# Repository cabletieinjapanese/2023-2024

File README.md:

repository for robocup bot, 2024 Singapore Robocup Open season

*updated 5 apr 2024*
## team, roles
loh hao yuan - elec, programming

lee yu zhe - mech, programming

cruz low, oliver ong - logistics, soldering

## final results
(5 apr 2024) 
due to a variety of factors (including misinterpretation of registration information, delays in robot production, lack of time for organiser to make adjustments), we were unable to participate in the 2024 Singapore Robocup Open.

throughout the past year, we've learnt a lot about the workings of a robocup bot, and we'll be back next year to finally prove our worth

we're currently working to finish up and polish our bot, such that we can run a few scrim games before starting anew with our bot for the 2024-2025 season.

## remarks
* everything here is half cooked spaghetti
    * we spent a lot of our time this year trying to figure things out, so a lot of stuff here is the result of trial and error
    * i guess our learning can be shown through the different versions, but theres many many areas which have a lot of potential for improvement
* version control
    * we didn't really use our github repository that much, which is a really bad practice
    * furthermore, one of our members has still not figured out how version control works, and consistently asks me to "help (him) push the code"  

## thanks
* [Sentinels Robotics](https://github.com/senrobo)
    * [@vincentcayadi](https://github.com/vincentcayadi) for his advice regarding the sport and life as a whole, his boundless enthusiasm, faith in our capabilities and good humour
    * [@shuanluck](https://github.com/shuanluck), [@DavidLow22](https://github.com/DavidLow22), and Tan Kian Wu for advice in all areas of robocup
* [Ducc Robotics](https://github.com/8076ducc)
    * [@neohaojun](https://github.com/neohaojun) for guidance and advice with regards to budgeting

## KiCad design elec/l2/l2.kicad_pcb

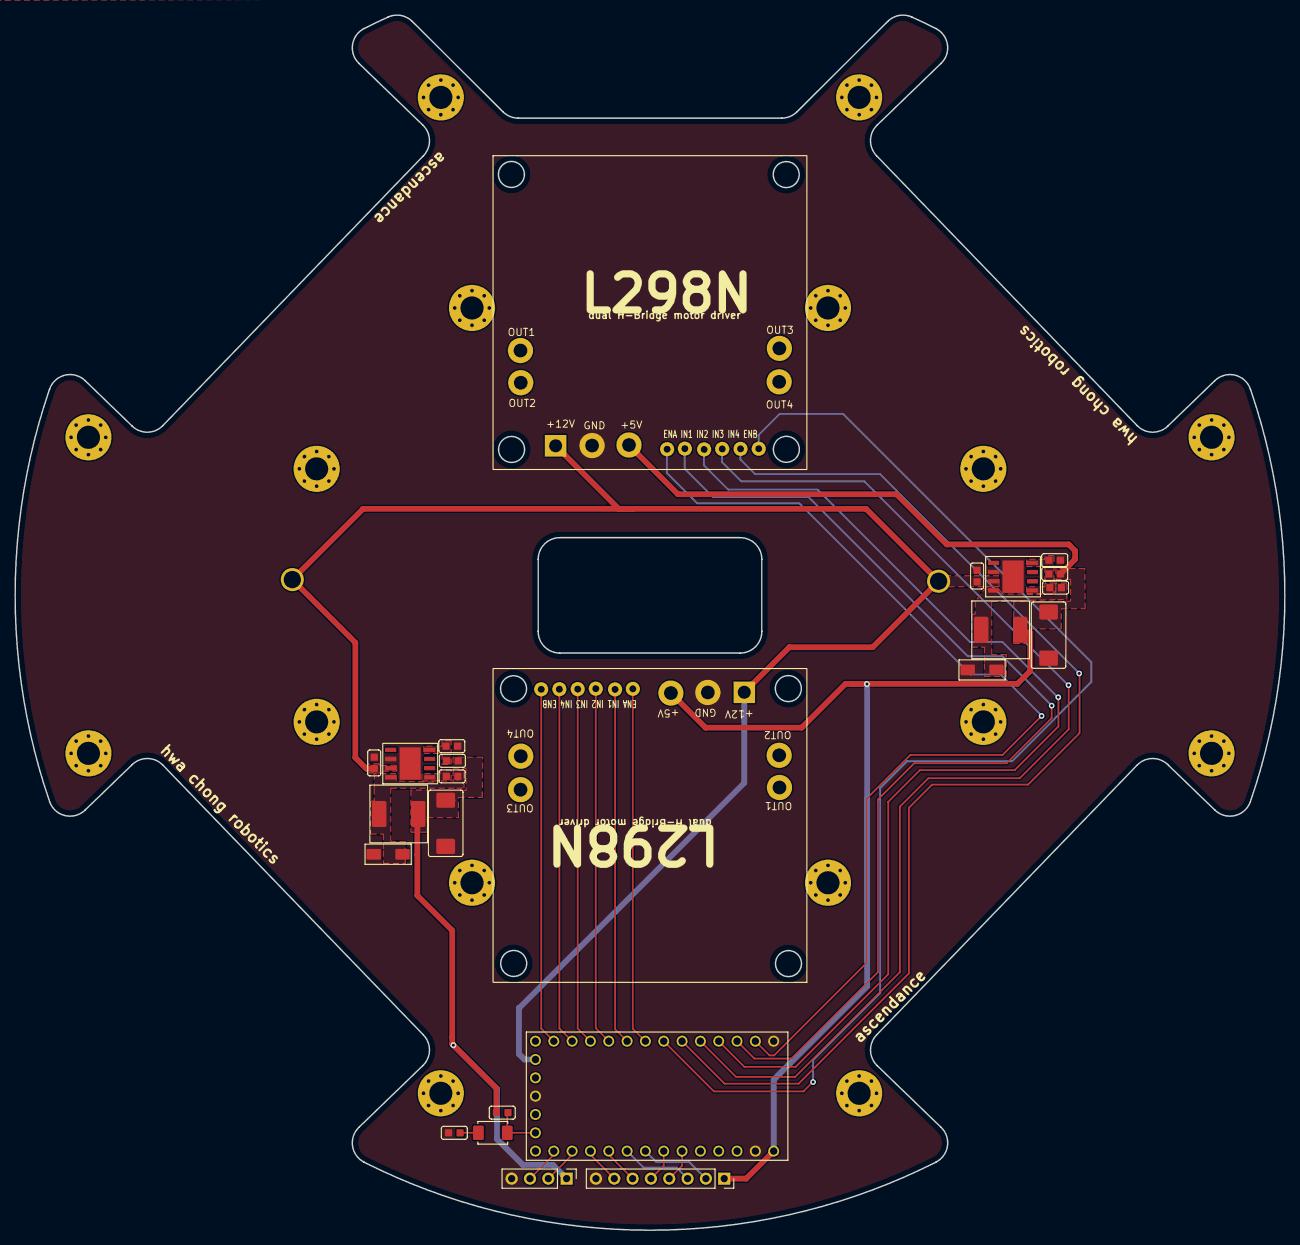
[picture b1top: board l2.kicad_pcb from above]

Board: 2 copper layers, 176.0 x 168.4 mm, 42 parts (0 on the bottom side), 32 nets.

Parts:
C1: 10n; cap0603
C2, C5: 220u; EIA-7343-D
C3, C6: C; cap0603
C4: 10u; cap0603
D1, D2: B340; DIOM5025X220N
H1, H2, H3, H4, H5, H6, H7, H8, H9, H10, H11, H12, H13, H14, H15, H16: MountingHole_Pad; MountingHole_3.2mm_M3_Pad_Via
J1, J2: Conn_01x13; L298N
J3: Conn_01x04; PinHeader_1x04_P2.54mm_Vertical
J5: Conn_01x08; PinSocket_1x08_P2.54mm_Vertical
L1, L2: 15uH; 0630 One Piece Inductor
R1, R3, R101: 10K; res0603
R2: 5K9; res0603
R4: 3K24; res0603
R102: 1K; res0603
SW101: SW_Push; SW_PUSH_SPST
U1, U3: TPS5430DDA; TI_SO-PowerPAD-8
U2: DEV-15583; MODULE_DEV-15583
batawg1, batawg2: +12V; 14 AWG

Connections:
+3V3: C5.1, J3.1, L2.2, R3.1, R101.1
+5V: C2.1, J1.5, J2.5, J5.1, L1.2, R1.1, U2.VIN
+12V: C3.1, C6.1, J1.3, J2.3, U1.7 (VIN), U2.VBAT, U3.7 (VIN), batawg1.1, batawg2.1
/1-ENA: J1.6, U2.0
/1-ENB: J1.11, U2.5
/1-IN1: J1.7, U2.1
/1-IN2: J1.8, U2.2
/1-IN3: J1.9, U2.3
/1-IN4: J1.10, U2.4
/2-ENA: J2.6, U2.6
/2-ENB: J2.11, U2.11
/2-IN1: J2.7, U2.7
/2-IN2: J2.8, U2.8
/2-IN3: J2.9, U2.9
/2-IN4: J2.10, U2.10
/C RX: J5.4, U2.21
/C TX: J5.5, U2.20
/COM SDA: J5.7, U2.16
/COM SDL: J5.6, U2.17
/L1RX: J3.3, U2.14
/L1TX: J3.2, U2.15
/RESET: R101.2, SW101.2, U2.ON-OFF (ON/OFF)
/TOF SCL: J5.2, U2.19
/TOF SDA: J5.3, U2.18
GND: C2.2, C3.2, C5.2, C6.2, D1.2 (A), D2.2 (A), J1.4, J2.4, J3.4, J5.8, R2.2, R4.2, R102.2, U1.6 (GND), U1.9 (GNDPAD), U2.G1, U2.G2, U2.G3, U3.6 (GND), U3.9 (GNDPAD)
unnamed: C1.2, D1.1 (K), L1.1, U1.8 (PH)
unnamed: C4.1, D2.1 (K), L2.1, U3.8 (PH)
unnamed: R102.1, SW101.1
unnamed: C1.1, U1.1 (BOOT)
unnamed: R1.2, R2.1, U1.4 (VSENSE)
unnamed: C4.2, U3.1 (BOOT)
unnamed: R3.2, R4.1, U3.4 (VSENSE)

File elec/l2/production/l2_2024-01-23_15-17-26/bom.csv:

Designator,Footprint,Quantity,Value,LCSC Part #
"AWG1, AWG2",14 AWG,2,MountingHole,
C1,cap0603,1,10n,
"C2, C5",EIA-7343-D,2,220u,
"C3, C6",cap0603,2,C,
C4,cap0603,1,10u,
"D1_2, D1",DIOM7959X265N,2,B340,
"H10, H11, H12, H13, H14, H3, H4, H5, H6, H7, H8, H9",MountingHole_3.2mm_M3_Pad_Via,12,MountingHole_Pad,
"J1, J2",L298N,2,Conn_01x06,
J3,PinSocket_1x04_P1.27mm_Vertical,1,Conn_01x04,
J5,PinSocket_1x08_P2.54mm_Vertical,1,Conn_01x08,
"L1, L2",0630 One Piece Inductor,2,15uH,
"R1, R101, R3",res0603,3,10K,
R102,res0603,1,1K,
R2,res0603,1,5K9,
R4,res0603,1,3K24,
SW101,SW_PUSH_SPST,1,SW_Push,
"U1, U3",TI_SO-PowerPAD-8,2,TPS5430DDA,
U2,MODULE_DEV-15583,1,DEV-15583,

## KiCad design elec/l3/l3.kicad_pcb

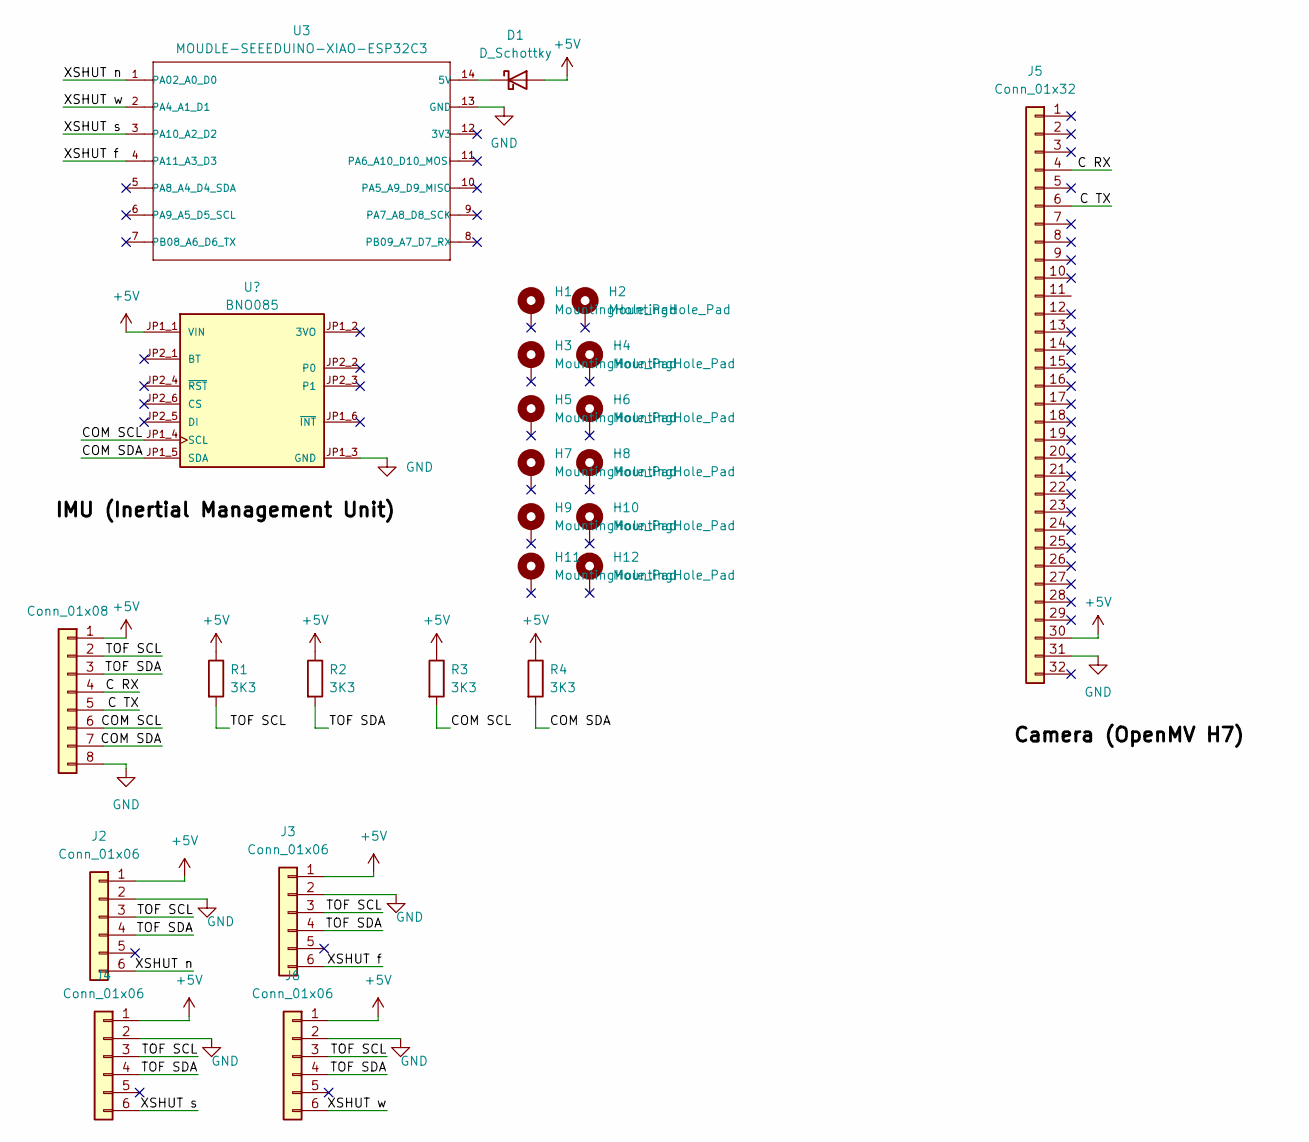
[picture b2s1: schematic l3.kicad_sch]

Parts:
D1: D_Schottky; D_0603_1608Metric_Pad1.05x0.95mm_HandSolder
H1, H2, H3, H4, H5, H6, H7, H8, H9, H10, H11, H12: MountingHole_Pad; MountingHole_3mm_Pad_Via
J1: Conn_01x08; PinSocket_1x08_P2.54mm_Vertical
J2, J3, J4, J6: Conn_01x06; PinSocket_1x06_P2.54mm_Vertical
J5: Conn_01x32; OpenMV_RT
R1, R2, R3, R4: 3K3; res0603
U2: BNO085; bno085; PARTREV 2021-03-16
U3: MOUDLE-SEEEDUINO-XIAO-ESP32C3; Seeeduino XIAO SAMD 21 TFT

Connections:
+5V: D1.2 (A), J1.1, J2.1, J3.1, J4.1, J5.30, J6.1, R1.1, R2.1, R3.1, R4.1, U2.JP1_1 (VIN)
/C RX: J1.4, J5.4
/C TX: J1.5, J5.6
/COM SCL: J1.6, R3.2, U2.JP1_4 (SCL)
/COM SDA: J1.7, R4.2, U2.JP1_5 (SDA)
/TOF SCL: J1.2, J2.3, J3.3, J4.3, J6.3, R1.2
/TOF SDA: J1.3, J2.4, J3.4, J4.4, J6.4, R2.2
/XSHUT f: J3.6, U3.4 (PA11_A3_D3)
/XSHUT n: J2.6, U3.1 (PA02_A0_D0)
/XSHUT s: J4.6, U3.3 (PA10_A2_D2)
/XSHUT w: J6.6, U3.2 (PA4_A1_D1)
GND: J1.8, J2.2, J3.2, J4.2, J5.31, J6.2, U2.JP1_3 (GND), U3.13 (GND)
unnamed: D1.1 (K), U3.14 (5V)

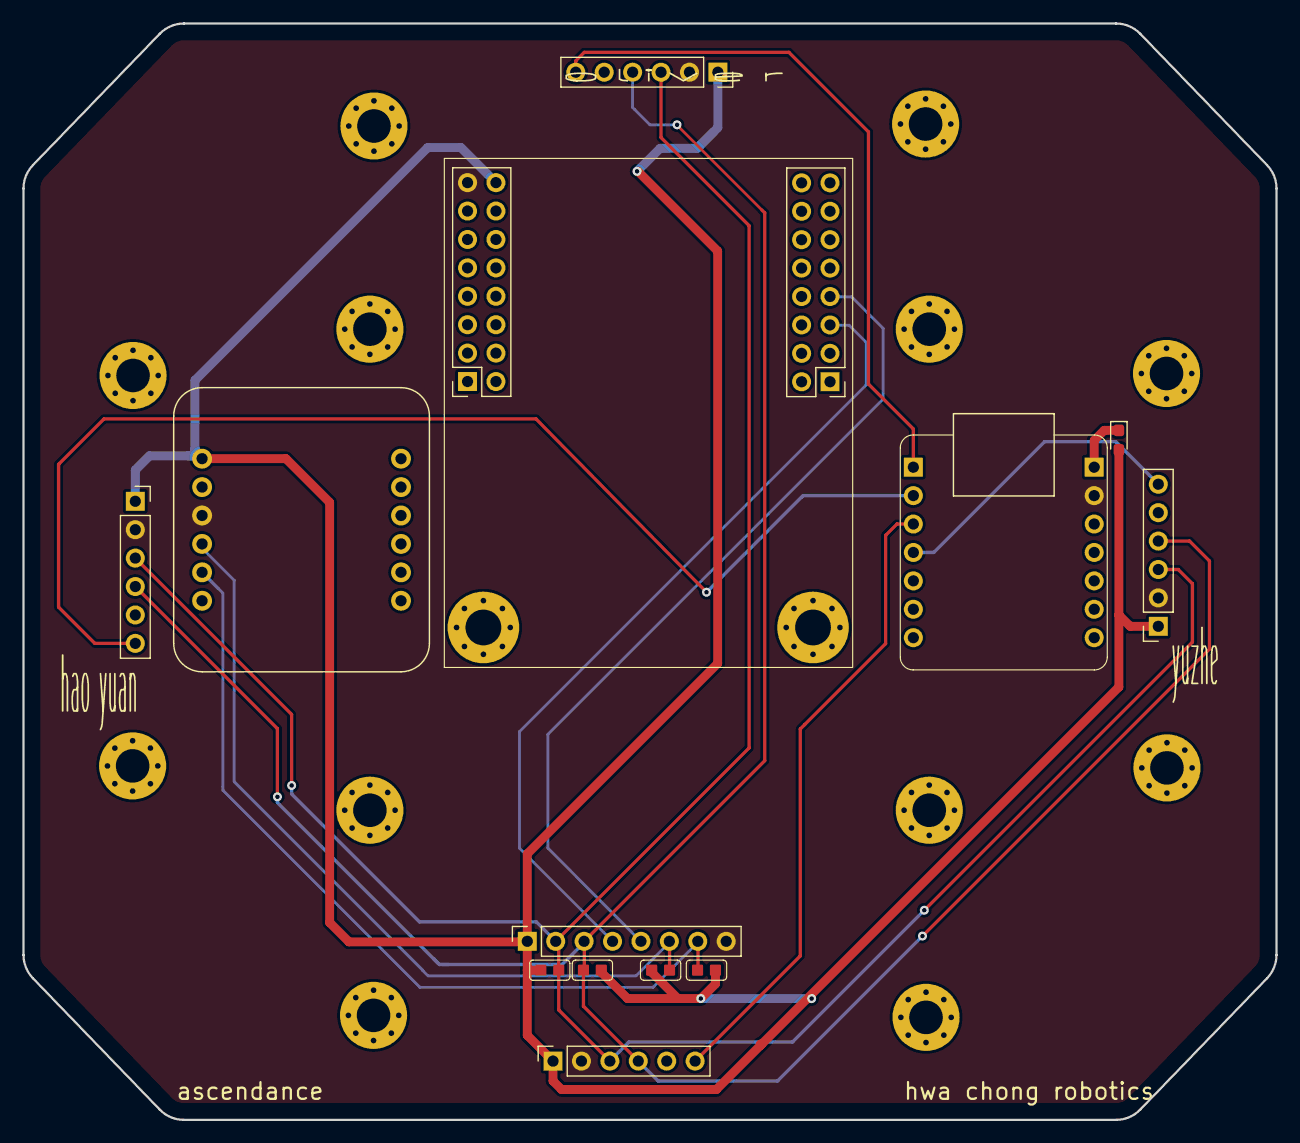
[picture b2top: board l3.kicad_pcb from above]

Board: 2 copper layers, 112.0 x 98.0 mm, 25 parts (0 on the bottom side), 13 nets.

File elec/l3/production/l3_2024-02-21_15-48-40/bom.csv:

Designator,Footprint,Quantity,Value,LCSC Part #
D1,0603,1,D_Schottky,
"H1, H10, H11, H12, H2, H3, H4, H5, H6, H7, H8, H9",MountingHole_3mm_Pad_Via,12,MountingHole_Pad,
J1,PinSocket_1x08_P2.54mm_Vertical,1,Conn_01x08,
"J2, J3, J4, J6",PinSocket_1x06_P2.54mm_Vertical,4,Conn_01x06,
J5,OpenMV_RT,1,Conn_01x32,
"R1, R2, R3, R4",res0603,4,3K3,
U2,bno085,1,BNO085,
U3,Seeeduino XIAO SAMD 21 TFT,1,MOUDLE-SEEEDUINO-XIAO-ESP32C3,

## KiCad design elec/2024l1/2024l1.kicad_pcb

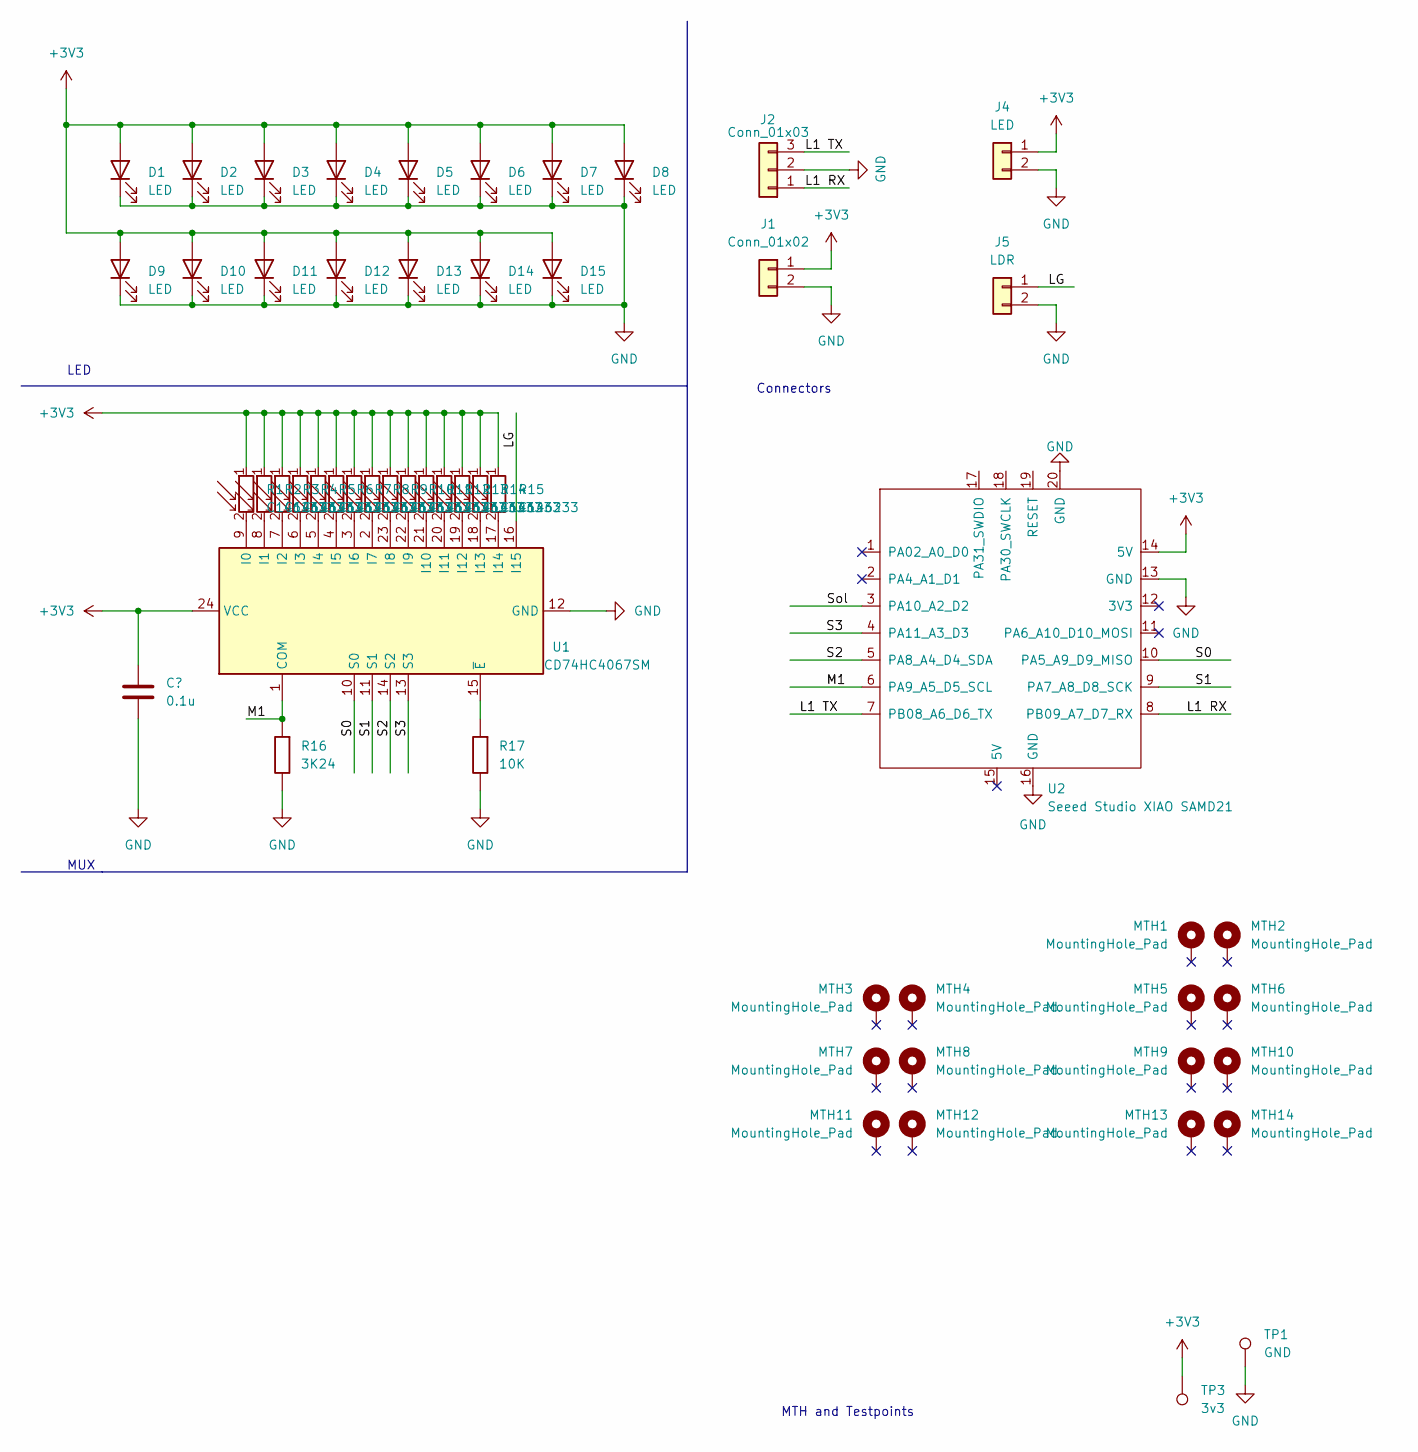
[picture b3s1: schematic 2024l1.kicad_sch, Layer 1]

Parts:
C1: 0.1u; cap0603; LCSC C5463924
D1, D2, D3, D4, D5, D6, D7, D8, D9, D10, D11, D12, D13, D14, D15: LED; led2835; LCSC C7423442
J1: Conn_01x02; JST_XH_B2B-XH-A_1x02_P2.50mm_Vertical
J2: Conn_01x03; JST_XH_B3B-XH-A_1x03_P2.50mm_Vertical; LCSC C144394
J4: LED; PinSocket_1x02_P2.54mm_Vertical
J5: LDR; PinSocket_1x02_P2.54mm_Vertical
MTH1, MTH2, MTH3, MTH4, MTH5, MTH6, MTH7, MTH8, MTH9, MTH10, MTH11, MTH12, MTH13, MTH14: MountingHole_Pad; MountingHole_3.2mm_M3_Pad_Via
R1, R2, R3, R4, R5, R6, R7, R8, R9, R10, R11, R12, R13, R14, R15: C146233; ALS-PT19 (Top Side); LCSC C146233
R16: 3K24; res0603; LCSC C22994
R17: 10K; res0603; LCSC C25804
TP1: GND; 14 AWG
TP3: 3v3; 14 AWG
U1: CD74HC4067SM; CD74HC4067M; LCSC C1545936
U2: Seeed Studio XIAO SAMD21; Seeeduino XIAO SAMD 21 TFT

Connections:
+3V3: C1.1, D1.2 (A), D2.2 (A), D3.2 (A), D4.2 (A), D5.2 (A), D6.2 (A), D7.2 (A), D8.2 (A), D9.2 (A), D10.2 (A), D11.2 (A), D12.2 (A), D13.2 (A), D14.2 (A), D15.2 (A), J1.1, J4.1, R1.1, R2.1, R3.1, R4.1, R5.1, R6.1, R7.1, R8.1, R9.1, R10.1, R11.1, R12.1, R13.1, R14.1, R15.1, TP3.1, U1.24 (VCC), U2.14 (5V)
/L1 RX: J2.1, U2.8 (PB09_A7_D7_RX)
/L1 TX: J2.3, U2.7 (PB08_A6_D6_TX)
/LG: J5.1, U1.16 (I15)
/M1: R16.2, U1.1 (COM), U2.6 (PA9_A5_D5_SCL)
/S0: U1.10 (S0), U2.10 (PA5_A9_D9_MISO)
/S1: U1.11 (S1), U2.9 (PA7_A8_D8_SCK)
/S2: U1.14 (S2), U2.5 (PA8_A4_D4_SDA)
/S3: U1.13 (S3), U2.4 (PA11_A3_D3)
/Sol: U2.3 (PA10_A2_D2)
GND: C1.2, D1.1 (K), D2.1 (K), D3.1 (K), D4.1 (K), D5.1 (K), D6.1 (K), D7.1 (K), D8.1 (K), D9.1 (K), D10.1 (K), D11.1 (K), D12.1 (K), D13.1 (K), D14.1 (K), D15.1 (K), J1.2, J2.2, J4.2, J5.2, R16.1, R17.1, TP1.1, U1.12 (GND), U2.13 (GND), U2.16 (GND), U2.20 (GND)
unnamed: R1.2, U1.9 (I0)
unnamed: R2.2, U1.8 (I1)
unnamed: R3.2, U1.7 (I2)
unnamed: R4.2, U1.6 (I3)
unnamed: R5.2, U1.5 (I4)
unnamed: R6.2, U1.4 (I5)
unnamed: R7.2, U1.3 (I6)
unnamed: R8.2, U1.2 (I7)
unnamed: R9.2, U1.23 (I8)
unnamed: R10.2, U1.22 (I9)
unnamed: R11.2, U1.21 (I10)
unnamed: R12.2, U1.20 (I11)
unnamed: R13.2, U1.19 (I12)
unnamed: R14.2, U1.18 (I13)
unnamed: R15.2, U1.17 (I14)
unnamed: R17.2, U1.15 (~E)

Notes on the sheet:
MUX
MTH and Testpoints
LED
Connectors

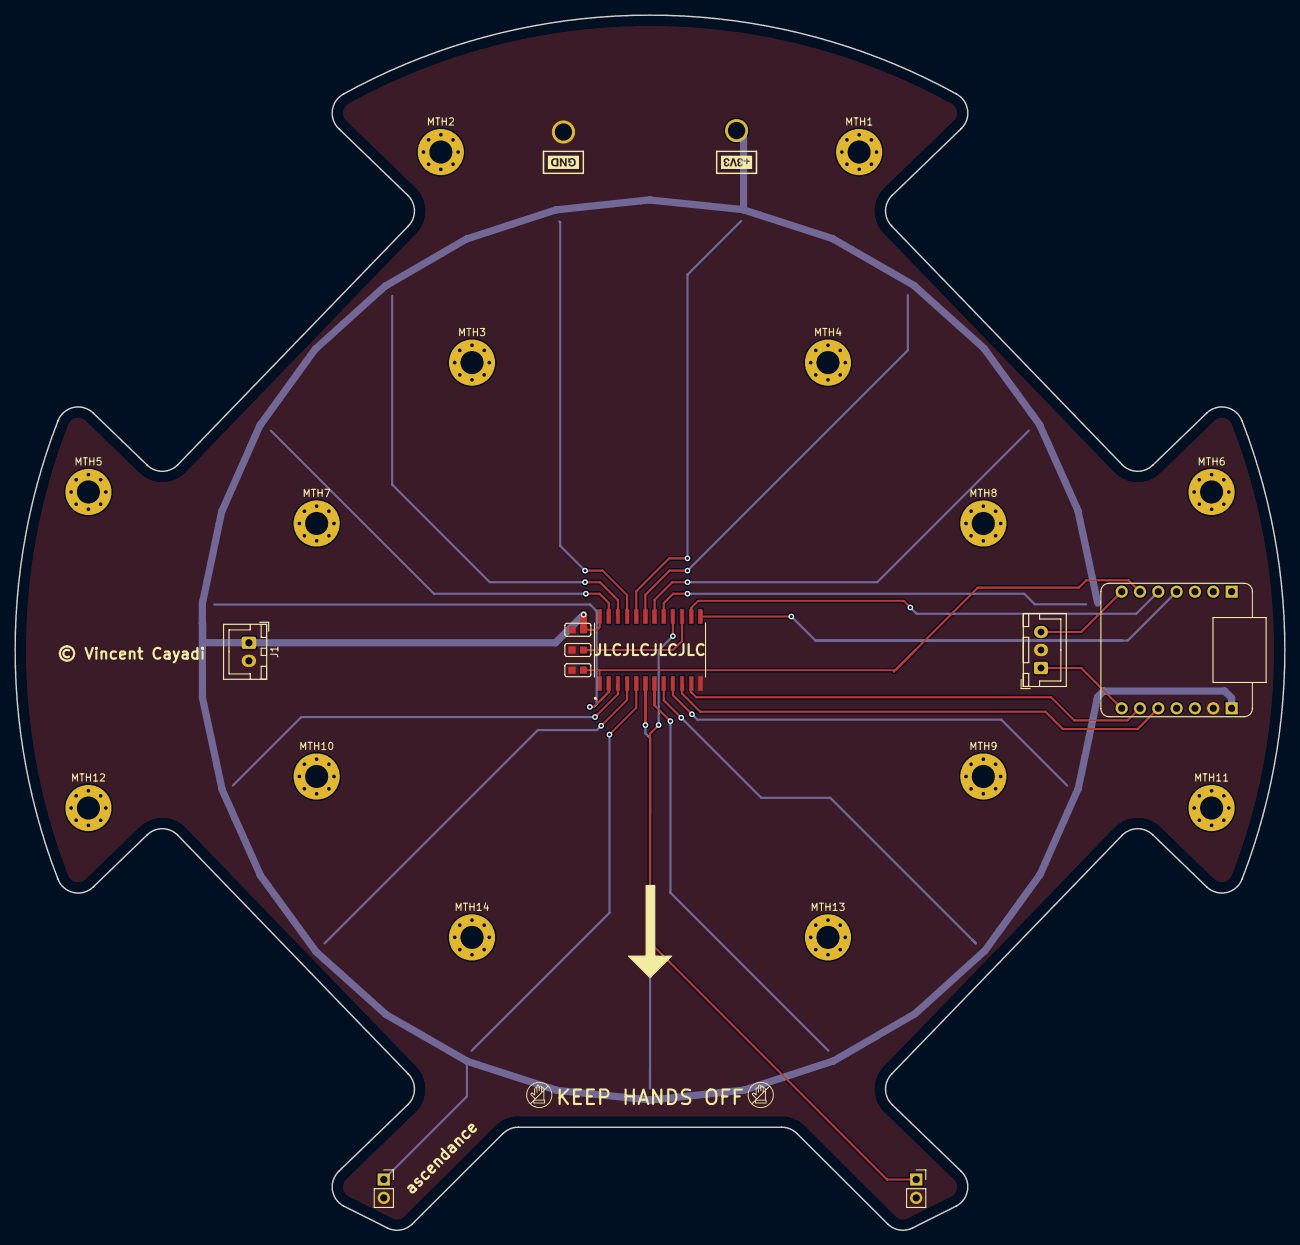
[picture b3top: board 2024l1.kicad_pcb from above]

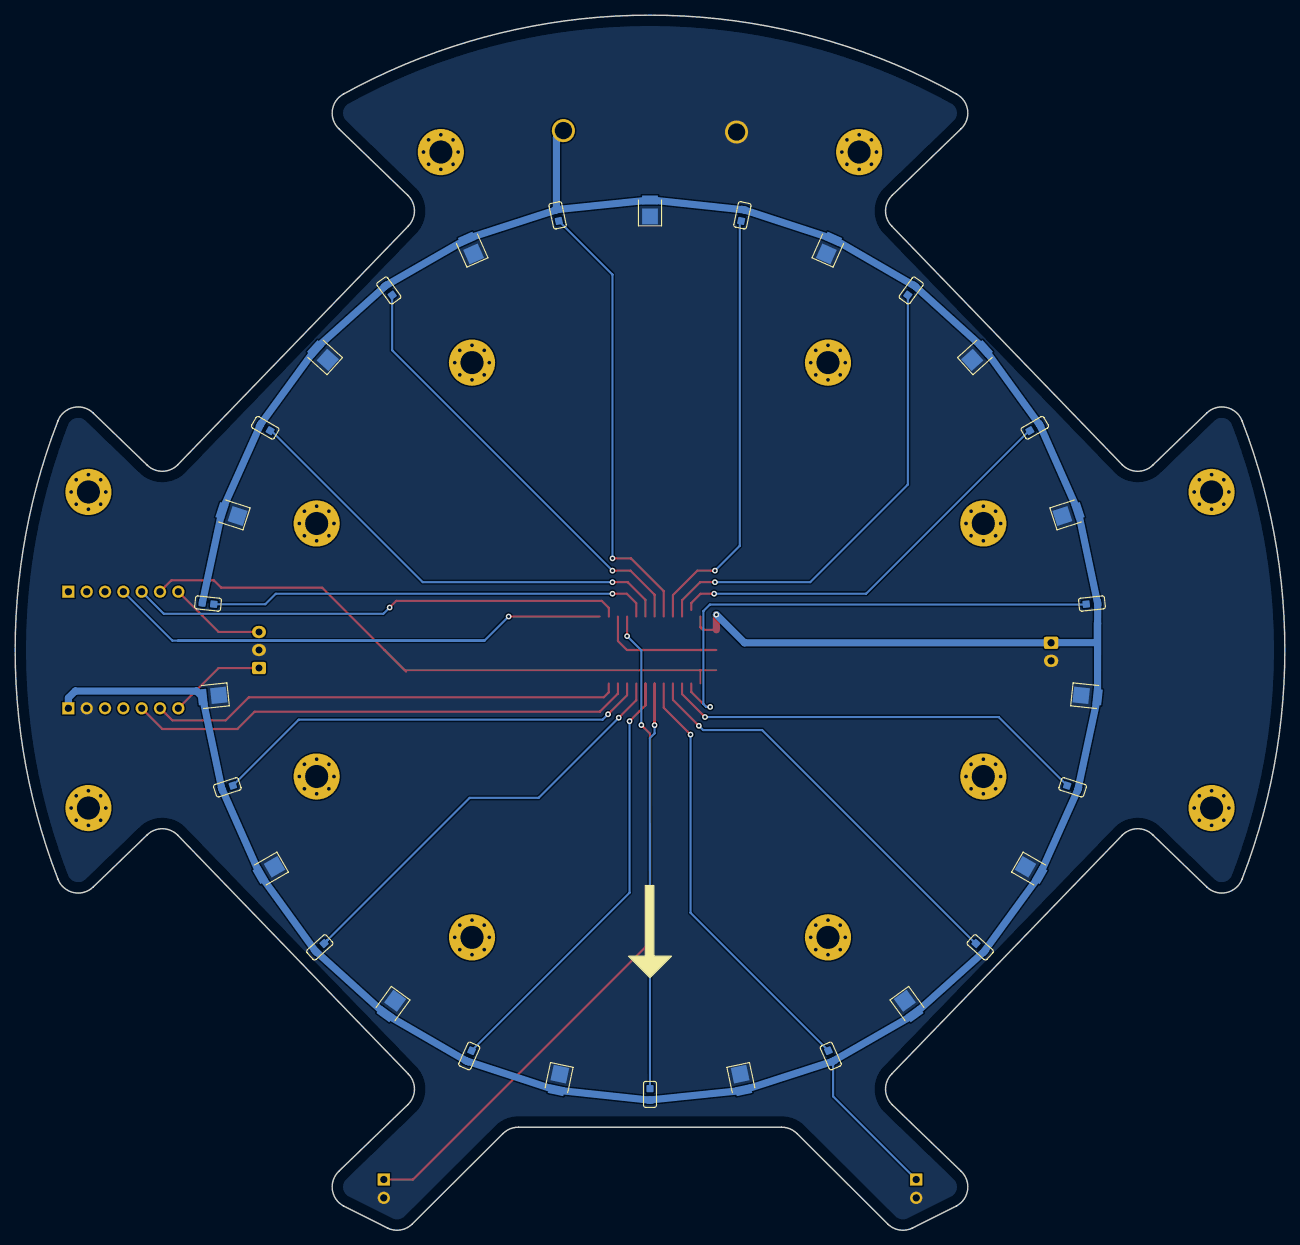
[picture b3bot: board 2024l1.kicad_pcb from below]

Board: 2 copper layers, 176.0 x 168.4 mm, 57 parts (30 on the bottom side), 26 nets.

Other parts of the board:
kibuzzard-655F61C6: G***; kibuzzard-655F61C6
kibuzzard-655F6265: G***; kibuzzard-655F6265

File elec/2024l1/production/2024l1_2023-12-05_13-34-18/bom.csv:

Designator,Footprint,Quantity,Value,LCSC Part #
C1,cap0603,1,0.1u,C5463924
"D1, D10, D11, D12, D13, D14, D15, D2, D3, D4, D5, D6, D7, D8, D9",led2835,15,LED,C7423442
J1,JST_XH_B2B-XH-A_1x02_P2.50mm_Vertical,1,Conn_01x02,
J2,JST_XH_B3B-XH-A_1x03_P2.50mm_Vertical,1,Conn_01x03,C144394
J4,PinSocket_1x02_P2.54mm_Vertical,1,LED,
J5,PinSocket_1x02_P2.54mm_Vertical,1,LDR,
"MTH1, MTH10, MTH11, MTH12, MTH13, MTH14, MTH2, MTH3, MTH4, MTH5, MTH6, MTH7, MTH8, MTH9",MountingHole_3.2mm_M3_Pad_Via,14,MountingHole_Pad,
"R1, R10, R11, R12, R13, R14, R15, R2, R3, R4, R5, R6, R7, R8, R9",ALS-PT19 (Top Side),15,C146233,C146233
R16,res0603,1,3K24,C22994
R17,res0603,1,10K,C25804
TP1,14 AWG,1,GND,
TP3,14 AWG,1,3v3,
U1,CD74HC4067M,1,CD74HC4067SM,C1545936
U2,Seeeduino XIAO SAMD 21 TFT,1,Seeed Studio XIAO SAMD21,

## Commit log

2023-07-07 brought files to new repo
2023-07-07 hamburger cheeseburger big mac whopper
    hamburger cheeseburger
2023-07-19 co
    coaeoo
2023-07-19 L2 net labels
2023-07-19 Revert "L2 net labels"
    This reverts commit 1f70947ea7bd54b8f040afb39f0aba0e0f35dfe9.
2023-07-19 I like monkey balls.
2023-07-19 I really like donkey pussy
2023-07-21 trololol
2023-07-21 Updated Thing
2023-07-25 activation circuit, motor drivers removed from l1
2023-07-25 STUFF
2023-07-26 Updated stuff
2023-12-10 v1.0 of L1 (sent to production), schematic for L2
2024-01-12 producion l1, fucked l2 need to redo, todo: l2,l3
2024-02-28 2024-02-28 production
2024-02-28 file organisation
2024-02-28 version control fixing
2024-02-28 survived the accidental commit of yuzhes entire laptop
2024-04-03 PROGGERS
2024-04-04 badonkers
2024-04-04 Bitch '
    '
2024-04-04 Update main.cpp
    should be studying for history :c

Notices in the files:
elec/2024l1/2024l1.kicad_pcb:
© Vincent Cayadi
